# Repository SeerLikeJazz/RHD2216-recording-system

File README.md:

> 2022.05.21，上海，疫情在家，整理一下研究生期间的部分工作……

*Project was part of my work while at:*
* [EE-MEMS LAB](https://mems.sjtu.edu.cn/)
* Department of Micro/Nano Electronics
* Shanghai Jiao Tong University
* 2016.09-2019.03
### 探针型柔性MEMS脑机接口器件及采集电路研究
#### 系统介绍
* 研制了一种超薄的柔性探针型神经信号采集电极。
* 搭建了植入式神经信号采集电路的系统平台。
* 利用研制的柔性探针型神经信号采集电极和神经信号采集电路的系统平台做了体外测试验证实验。
#### 采集电路
电路主要包括Intan Technologies公司的16通道前端微弱生理信号采集芯片RHD2116，核心控制单元采用ST公司主频168M的STM32F407微控制器，数据传输采用内部集成全硬件TCP/IP协议栈+MAC+PHY以太网接口芯片W5500，通过UDP协议的方式实现硬件系统与上位机通信。

> 系统框图

电路尺寸4.2cm x 4.2cm，重量22g（包含电池），可以非常轻便地用于脑机接口应用和生物学实验。实验表明，16通道的采集系统输入噪声低至7 μV，每通道采样频率高达20 kHz，采样分辨率16位，满足植入式神经信号采集的要求。

> 硬件顶、底视图

#### 柔性电极
器件整体全部采用生物相容性材料，Au（厚度300nm）作为引线、电极点和焊盘，Parylene（厚度4μm）作为基底和绝缘层，PEG作为粘结材料贴附电极于PI管上，PI管（外径330μm）用作辅助植入的支撑材料。

通过电化学沉积导电聚合物PEDOT:PSS来提高了电极的电化学性能，并通过500次的循环伏安测试和10分钟的超声处理，验证了修饰后的电极的电化学稳定和聚合物结合力稳定性，测试并分析了电极的伏安特性和电化学阻抗谱。

研究了通过生物相容性的材料和PI管的组合，改进了柔性电极的准确植入位置的方法。

> 电极工艺图

> 电极实物图

> 电化学测试

> 电极贴附示意图

#### 实验测试
为了验证从电极前端到采集电路后端整个系统的准确性和功能稳定性，使用琼脂和PBS溶液模拟脑组织的环境，验证柔性微电极的准确植入性，辅助使用PI管和柔性电极在环境中的分离状况；使用微小信号发生器模拟了神经信号的幅值和频率，在体外模拟的脑组织环境中测试了信号采集、数据预处理、数据传输到上位机和上位机实时波形显示的在线实验。

> 测试实验示意图

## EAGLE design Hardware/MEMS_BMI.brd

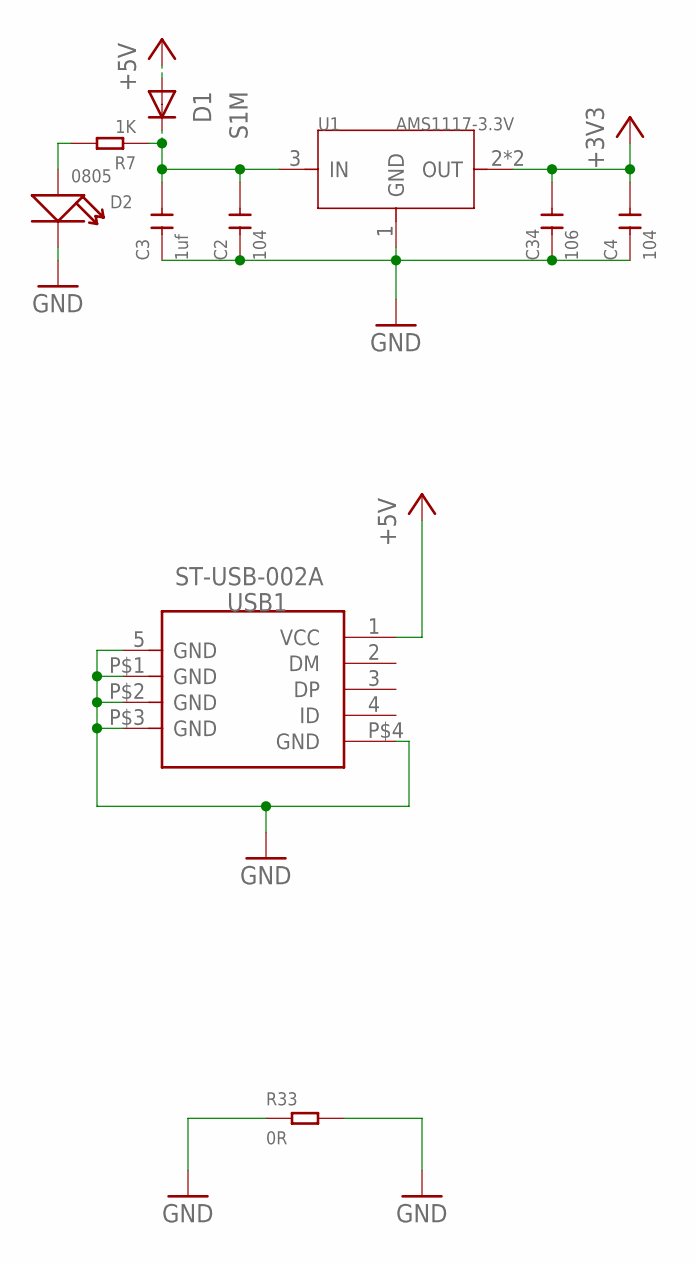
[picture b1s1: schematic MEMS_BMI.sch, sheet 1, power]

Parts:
C2, C4: 104; C0603
C3: 1uf; C0805
C34: 106; C0805
D1: S1M; SMA
D2: 0805; LED-0805
R7: 1K; R0603
R33: 0R; R0603
U1: AMS1117-3.3V; SOT-223
USB1: ST-USB-002A; MINIUSB5+4P-SMD-0.8-90D

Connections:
+3V3: C4.2, C34.2, U1.2 (OUT), U1.TER (OUT); also elsewhere on the board
+5V: D1.A, USB1.1 (VCC)
GND: C2.1, C3.1, C4.1, C34.1, D2.-, R33.1, R33.2, U1.1 (GND), USB1.5 (GND), USB1.P$1 (GND), USB1.P$2 (GND), USB1.P$3 (GND), USB1.P$4 (GND); also elsewhere on the board
unnamed: C2.2, C3.2, D1.C, R7.1, U1.3 (IN)
unnamed: D2.+, R7.2

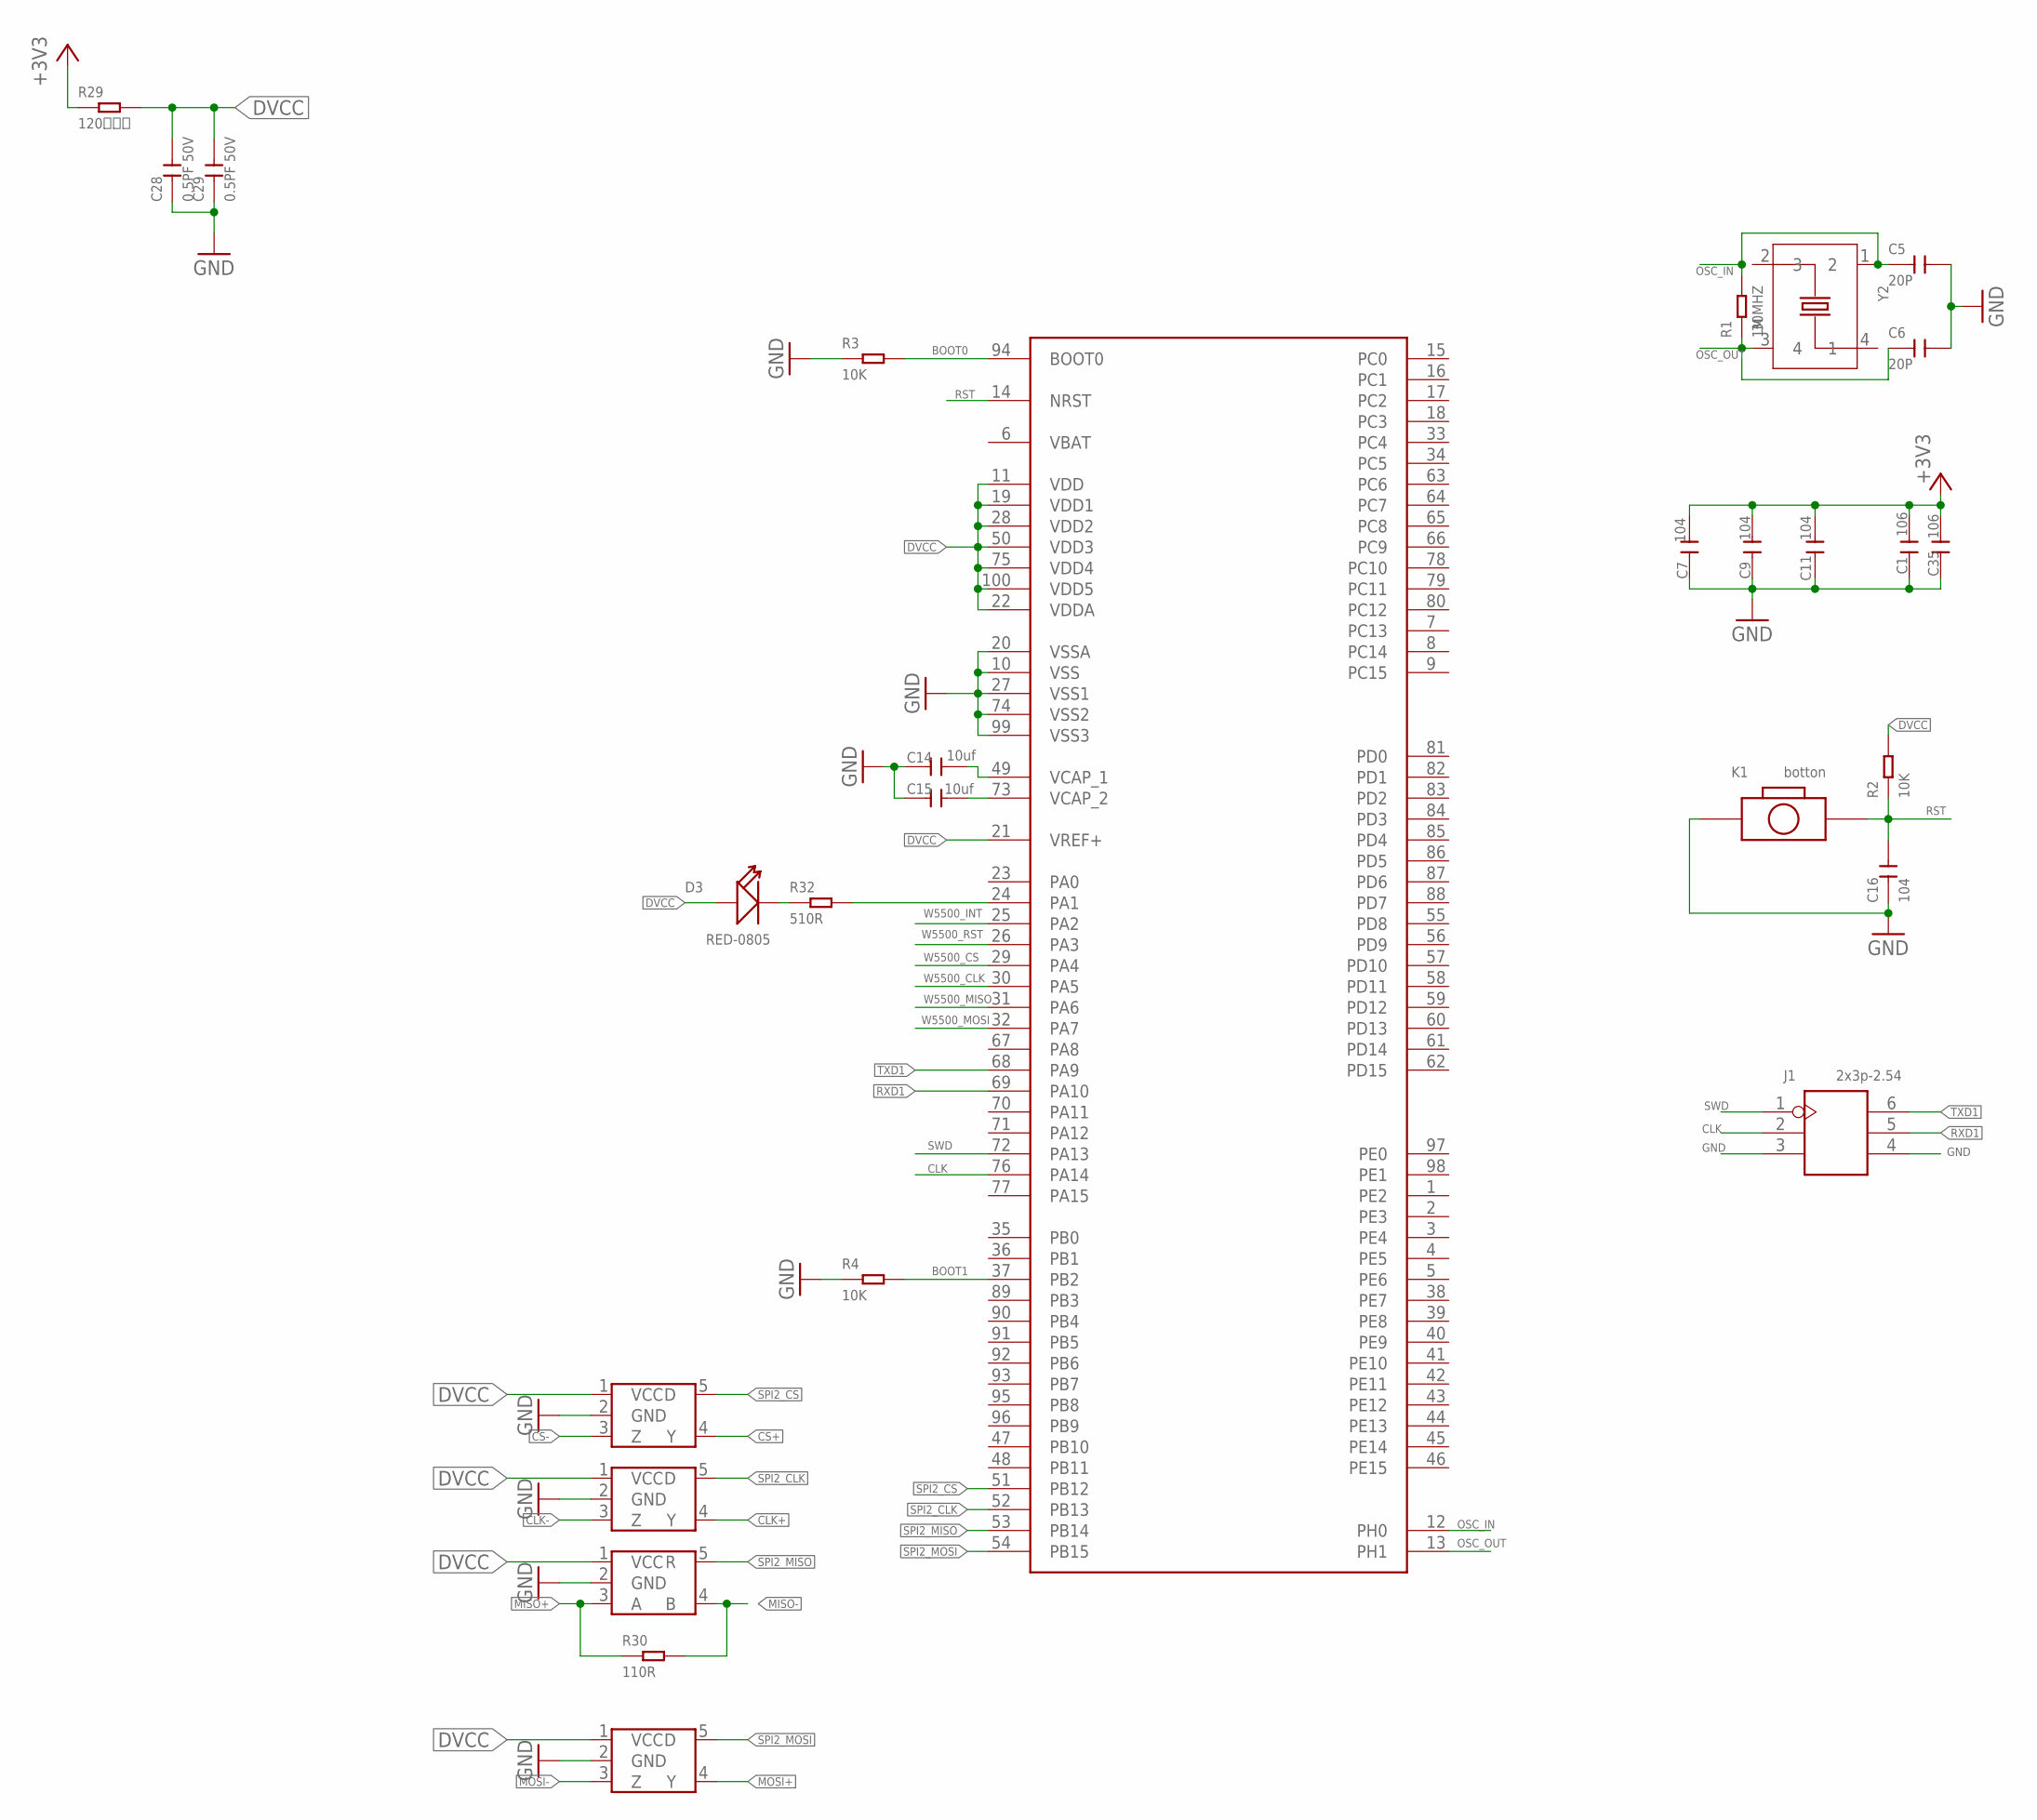
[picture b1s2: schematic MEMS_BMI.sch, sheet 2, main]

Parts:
C1, C35: 106; C0805
C5, C6: 20P; C0603
C7, C9, C11, C16: 104; C0603
C14, C15: 10uf; C0805
C28, C29: 0.5PF 50V; C0603
D3: RED-0805; LED-0805
J1: 2x3p-2.54; H2X3-2.54
K1: botton; SW2-SMD-3.0X6.0*2.5
LVDS1-1, LVDS1-2, LVDS1-3: SN65LVDS1; DBV_R-PDSO-G5
R1: 1M; R0603
R2, R3, R4: 10K; R0603
R29: 120欧磁珠; R0603
R30: 110R; R0603
R32: 510R; R0603
U$1: STM32F40XSTM32D40X; LQFP100
U$2: SN65LVDS2; DBV_R-PDSO-G5
Y2: 30MHZ; X4-SMD-3.2X2.5X0.7MM

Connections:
+3V3: C1.2, C7.1, C9.1, C11.1, C35.2, R29.1; also elsewhere on the board
BOOT0: R3.2, U$1.94 (BOOT0)
BOOT1: R4.2, U$1.37 (PB2)
CLK: J1.2, U$1.76 (PA14)
CLK+: LVDS1-2.4 (Y); also elsewhere on the board
CLK-: LVDS1-2.3 (Z); also elsewhere on the board
CS+: LVDS1-1.4 (Y); also elsewhere on the board
CS-: LVDS1-1.3 (Z); also elsewhere on the board
DVCC: C28.2, C29.2, D3.+, LVDS1-1.1 (VCC), LVDS1-2.1 (VCC), LVDS1-3.1 (VCC), R2.2, R29.2, U$1.11 (VDD), U$1.19 (VDD1), U$1.21 (VREF+), U$1.22 (VDDA), U$1.28 (VDD2), U$1.50 (VDD3), U$1.75 (VDD4), U$1.100 (VDD5), U$2.1 (VCC); also elsewhere on the board
GND: C1.1, C5.2, C6.2, C7.2, C9.2, C11.2, C14.1, C15.1, C16.1, C28.1, C29.1, C35.1, J1.3, J1.4, K1.1, LVDS1-1.2 (GND), LVDS1-2.2 (GND), LVDS1-3.2 (GND), R3.1, R4.1, U$1.10 (VSS), U$1.20 (VSSA), U$1.27 (VSS1), U$1.74 (VSS2), U$1.99 (VSS3), U$2.2 (GND); also elsewhere on the board
MISO+: R30.1, U$2.3 (A); also elsewhere on the board
MISO-: R30.2, U$2.4 (B); also elsewhere on the board
MOSI+: LVDS1-3.4 (Y); also elsewhere on the board
MOSI-: LVDS1-3.3 (Z); also elsewhere on the board
unnamed: C15.2, U$1.73 (VCAP_2)
unnamed: C14.2, U$1.49 (VCAP_1)
unnamed: D3.-, R32.1
unnamed: R32.2, U$1.24 (PA1)
OSC_IN: C5.1, R1.2, U$1.12 (PH0), Y2.1 (2)
OSC_OUT: C6.1, R1.1, U$1.13 (PH1), Y2.3 (4)
RST: C16.2, K1.2, R2.1, U$1.14 (NRST)
RXD1: J1.5, U$1.69 (PA10)
SPI2_CLK: LVDS1-2.5 (D), U$1.52 (PB13)
SPI2_CS: LVDS1-1.5 (D), U$1.51 (PB12)
SPI2_MISO: U$1.53 (PB14), U$2.5 (R)
SPI2_MOSI: LVDS1-3.5 (D), U$1.54 (PB15)
SWD: J1.1, U$1.72 (PA13)
TXD1: J1.6, U$1.68 (PA9)
W5500_CLK: U$1.30 (PA5); also elsewhere on the board
W5500_CS: U$1.29 (PA4); also elsewhere on the board
W5500_INT: U$1.25 (PA2); also elsewhere on the board
W5500_MISO: U$1.31 (PA6); also elsewhere on the board
W5500_MOSI: U$1.32 (PA7); also elsewhere on the board
W5500_RST: U$1.26 (PA3); also elsewhere on the board

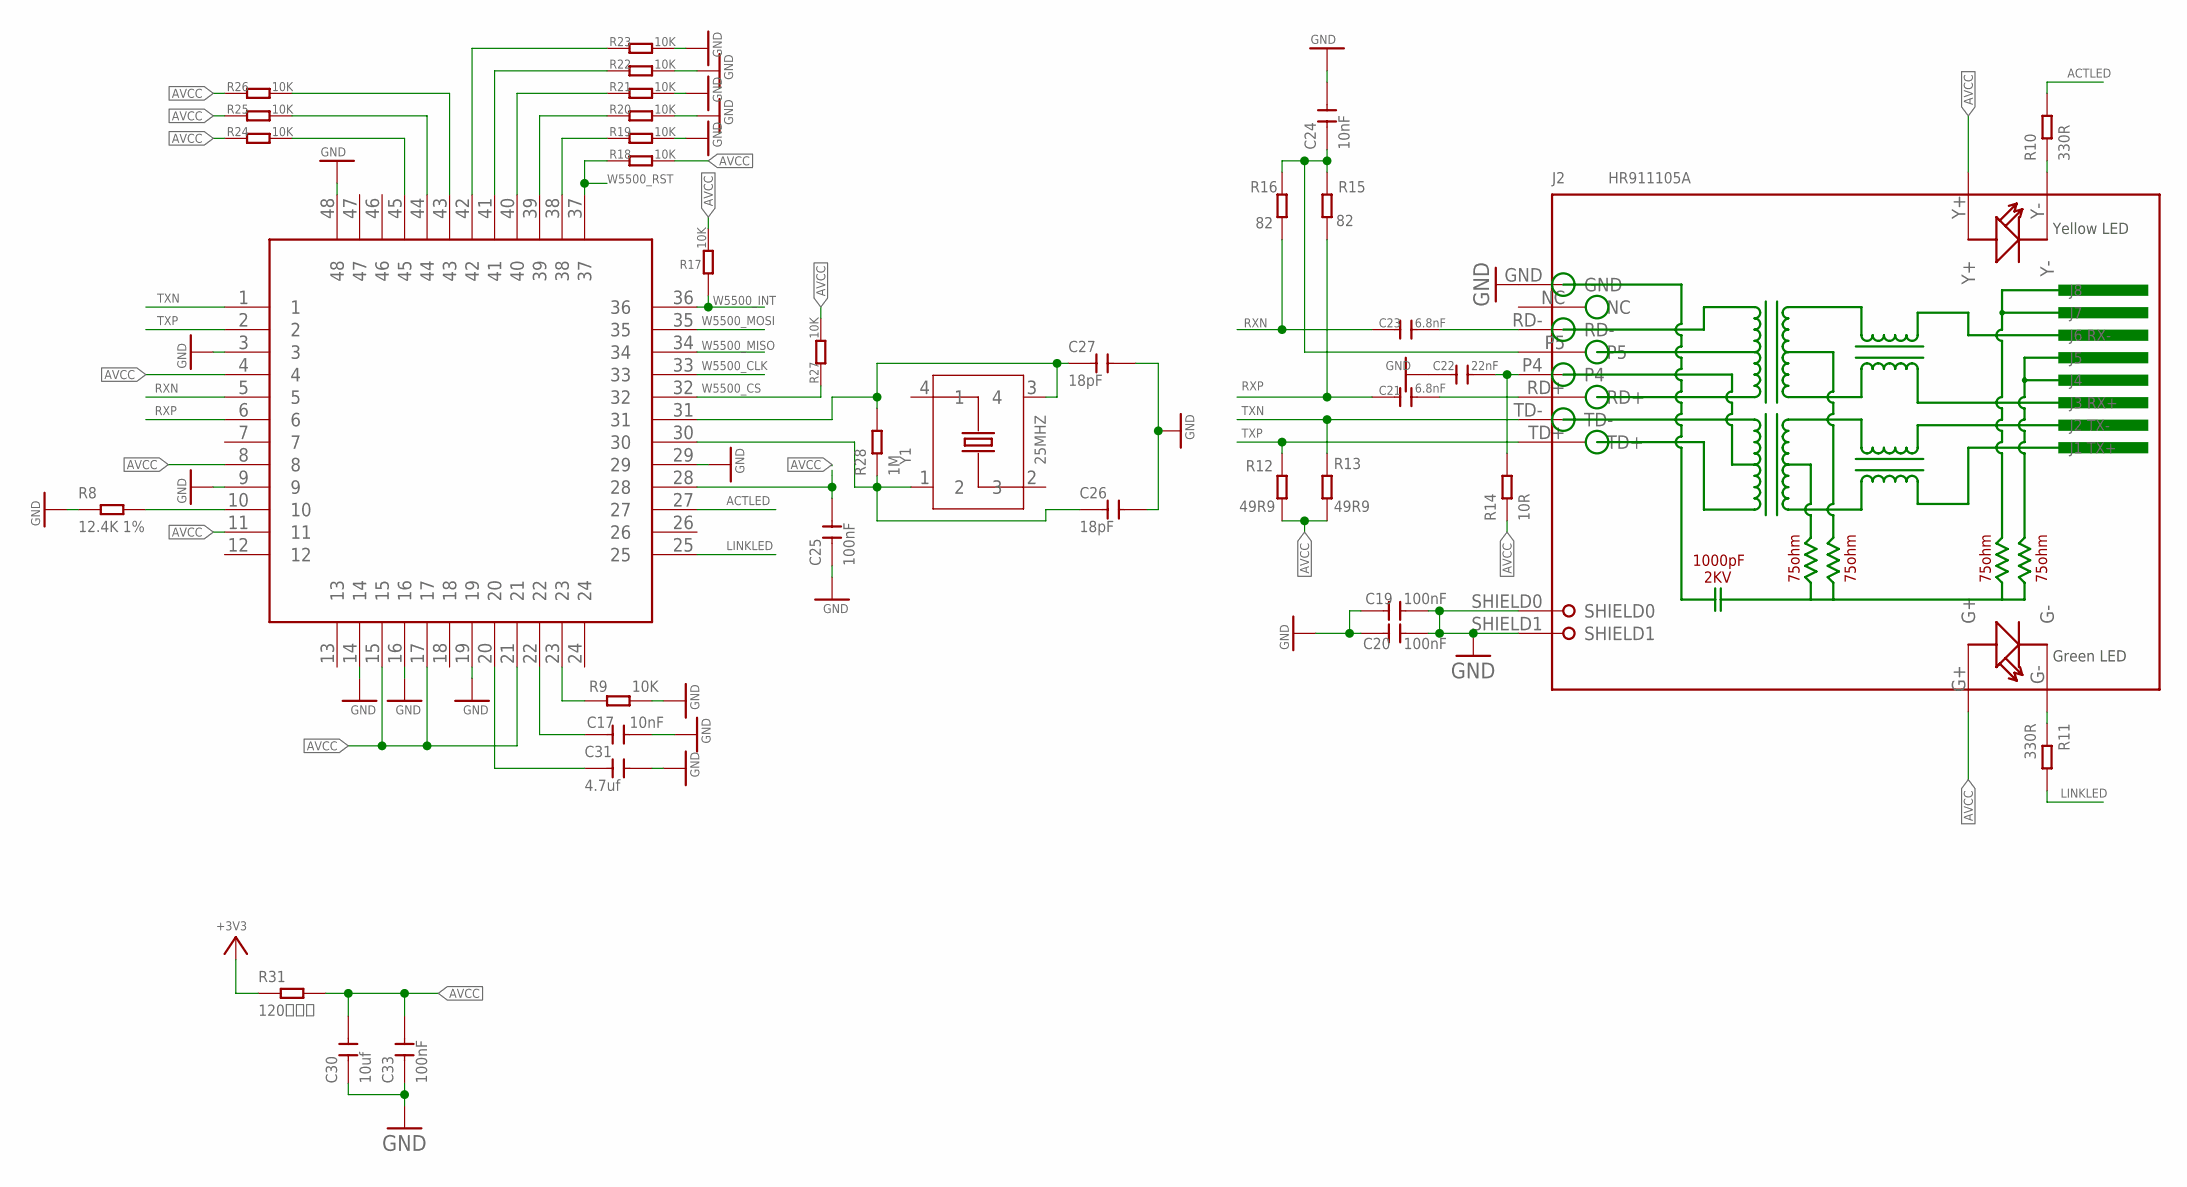
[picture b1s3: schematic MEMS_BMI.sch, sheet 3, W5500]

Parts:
C17, C24: 10nF; C0603
C19, C20, C25, C33: 100nF; C0603
C21, C23: 6.8nF; C0603
C22: 22nF; C0603
C26, C27: 18pF; C0603
C30: 10uf; C0805
C31: 4.7uf; C0805
J2: HR911105A; RJ45-12+2P-21.3X16.04X13.4MM
R8: 12.4K 1%; R0603
R9, R17, R18, R19, R20, R21, R22, R23, R24, R25, R26, R27: 10K; R0603
R10, R11: 330R; R0603
R12, R13: 49R9; R0603
R14: 10R; R0603
R15, R16: 82; R0603
R28: 1M; R0603
R31: 120欧磁珠; R0603
W5500-1: W5500; LQFP48
Y1: 25MHZ; X4-SMD-3.2X2.5X0.7MM

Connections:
+3V3: R31.1; also elsewhere on the board
ACTLED: R10.2, W5500-1.27
AVCC: C25.2, C30.2, C33.2, J2.G+, J2.Y+, R12.1, R13.1, R14.1, R17.2, R18.2, R24.1, R25.1, R26.1, R27.2, R31.2, W5500-1.4, W5500-1.8, W5500-1.11, W5500-1.15, W5500-1.17, W5500-1.21, W5500-1.28
GND: C17.2, C19.1, C19.2, C20.1, C20.2, C22.1, C24.2, C25.1, C26.2, C27.2, C30.1, C31.2, C33.1, J2.GND, J2.SHIELD0, J2.SHIELD1, R8.1, R9.2, R19.2, R20.2, R21.2, R22.2, R23.2, W5500-1.3, W5500-1.9, W5500-1.14, W5500-1.16, W5500-1.19, W5500-1.29, W5500-1.48; also elsewhere on the board
LINKLED: R11.2, W5500-1.25
unnamed: R9.1, W5500-1.23
unnamed: C17.1, W5500-1.22
unnamed: C31.1, W5500-1.20
unnamed: J2.G-, R11.1
unnamed: J2.Y-, R10.1
unnamed: R24.2, W5500-1.45
unnamed: R8.2, W5500-1.10
unnamed: R25.2, W5500-1.44
unnamed: C21.2, J2.RD+
unnamed: C22.2, J2.P4, R14.2
unnamed: R26.2, W5500-1.43
unnamed: C23.2, J2.RD-
unnamed: C27.1, R28.2, W5500-1.31, Y1.3 (4)
unnamed: R19.1, W5500-1.38
unnamed: C24.1, J2.P5, R15.2, R16.2
unnamed: R20.1, W5500-1.39
unnamed: R21.1, W5500-1.40
unnamed: R22.1, W5500-1.41
unnamed: R23.1, W5500-1.42
unnamed: C26.1, R28.1, W5500-1.30, Y1.1 (2)
RXN: C23.1, R16.1, W5500-1.5
RXP: C21.1, R15.1, W5500-1.6
TXN: J2.TD-, R13.2, W5500-1.1
TXP: J2.TD+, R12.2, W5500-1.2
W5500_CLK: W5500-1.33; also elsewhere on the board
W5500_CS: R27.1, W5500-1.32; also elsewhere on the board
W5500_INT: R17.1, W5500-1.36; also elsewhere on the board
W5500_MISO: W5500-1.34; also elsewhere on the board
W5500_MOSI: W5500-1.35; also elsewhere on the board
W5500_RST: R18.1, W5500-1.37; also elsewhere on the board

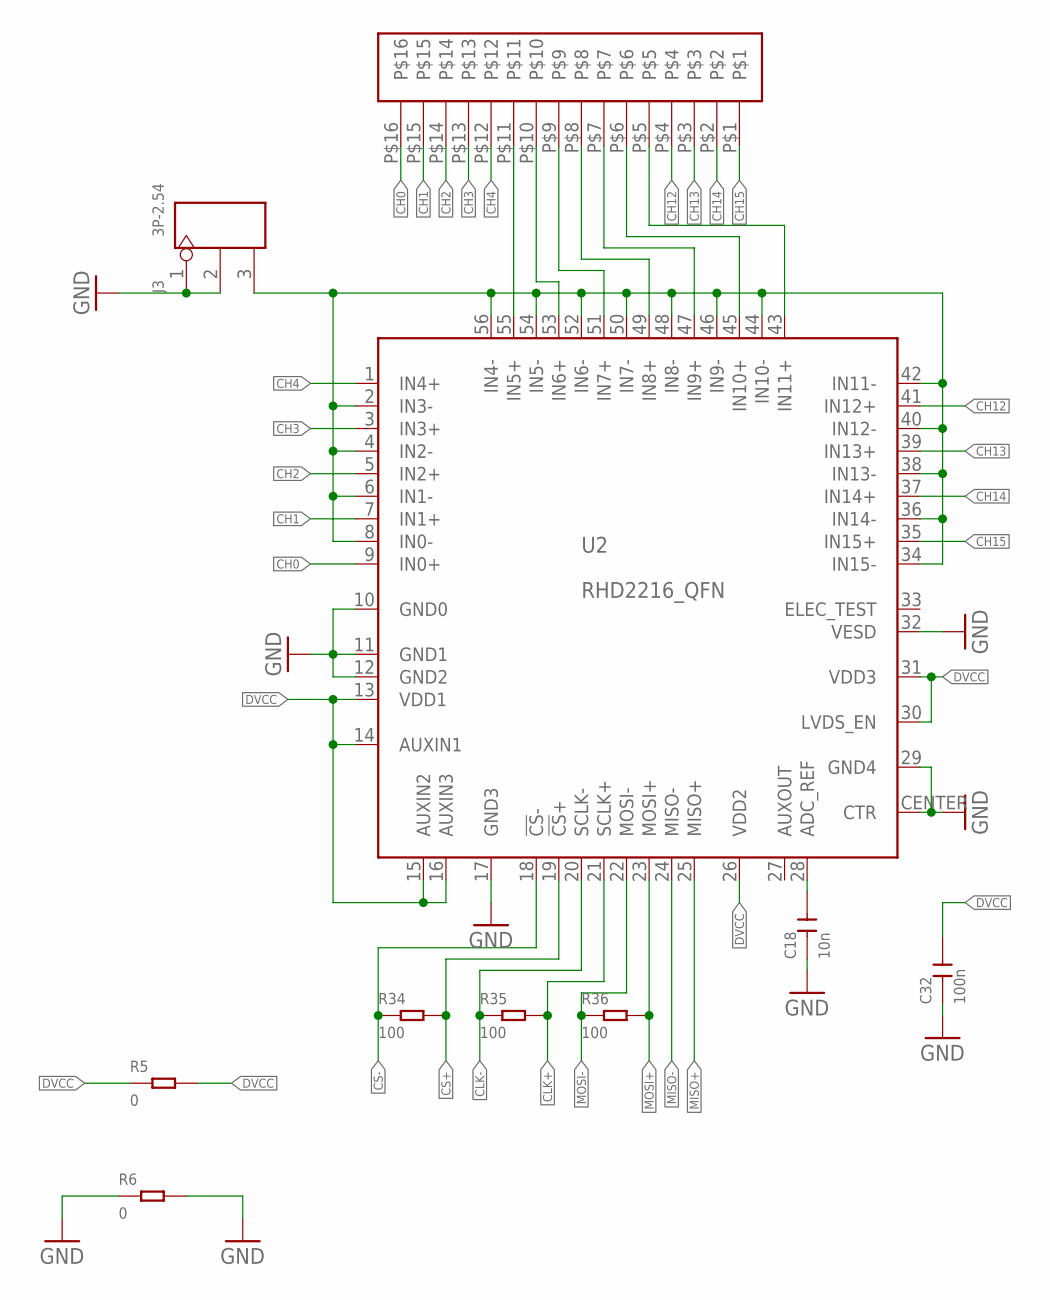
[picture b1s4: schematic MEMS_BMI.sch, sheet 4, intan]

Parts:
C18: 10n; C0603
C32: 100n; C0603
J3: 3P-2.54; H3-2.54
R5, R6: 0; R0603
R34, R35, R36: 100; R0603
U2: RHD2216_QFN; QFN56_8_X_8_LARGE
U$3: PROBE; PROBE-16-PIN

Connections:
CH0: U2.9 (IN0+), U$3.P$16
CH1: U2.7 (IN1+), U$3.P$15
CH2: U2.5 (IN2+), U$3.P$14
CH3: U2.3 (IN3+), U$3.P$13
CH4: U2.1 (IN4+), U$3.P$12
CH12: U2.41 (IN12+), U$3.P$4
CH13: U2.39 (IN13+), U$3.P$3
CH14: U2.37 (IN14+), U$3.P$2
CH15: U2.35 (IN15+), U$3.P$1
CLK+: R35.2, U2.21 (SCLK+); also elsewhere on the board
CLK-: R35.1, U2.20 (SCLK-); also elsewhere on the board
CS+: R34.2, U2.19 (!CS!+); also elsewhere on the board
CS-: R34.1, U2.18 (!CS!-); also elsewhere on the board
DVCC: C32.2, R5.1, R5.2, U2.13 (VDD1), U2.14 (AUXIN1), U2.15 (AUXIN2), U2.16 (AUXIN3), U2.26 (VDD2), U2.30 (LVDS_EN), U2.31 (VDD3); also elsewhere on the board
GND: C18.1, C32.1, J3.1, J3.2, R6.1, R6.2, U2.10 (GND0), U2.11 (GND1), U2.12 (GND2), U2.17 (GND3), U2.29 (GND4), U2.32 (VESD), U2.CENTER (CTR); also elsewhere on the board
MISO+: U2.25 (MISO+); also elsewhere on the board
MISO-: U2.24 (MISO-); also elsewhere on the board
MOSI+: R36.2, U2.23 (MOSI+); also elsewhere on the board
MOSI-: R36.1, U2.22 (MOSI-); also elsewhere on the board
unnamed: C18.2, U2.28 (ADC_REF)
unnamed: J3.3, U2.2 (IN3-), U2.4 (IN2-), U2.6 (IN1-), U2.8 (IN0-), U2.34 (IN15-), U2.36 (IN14-), U2.38 (IN13-), U2.40 (IN12-), U2.42 (IN11-), U2.44 (IN10-), U2.46 (IN9-), U2.48 (IN8-), U2.50 (IN7-), U2.52 (IN6-), U2.54 (IN5-), U2.56 (IN4-)
unnamed: U2.55 (IN5+), U$3.P$11
unnamed: U2.53 (IN6+), U$3.P$10
unnamed: U2.51 (IN7+), U$3.P$9
unnamed: U2.49 (IN8+), U$3.P$8
unnamed: U2.47 (IN9+), U$3.P$7
unnamed: U2.45 (IN10+), U$3.P$6
unnamed: U2.43 (IN11+), U$3.P$5

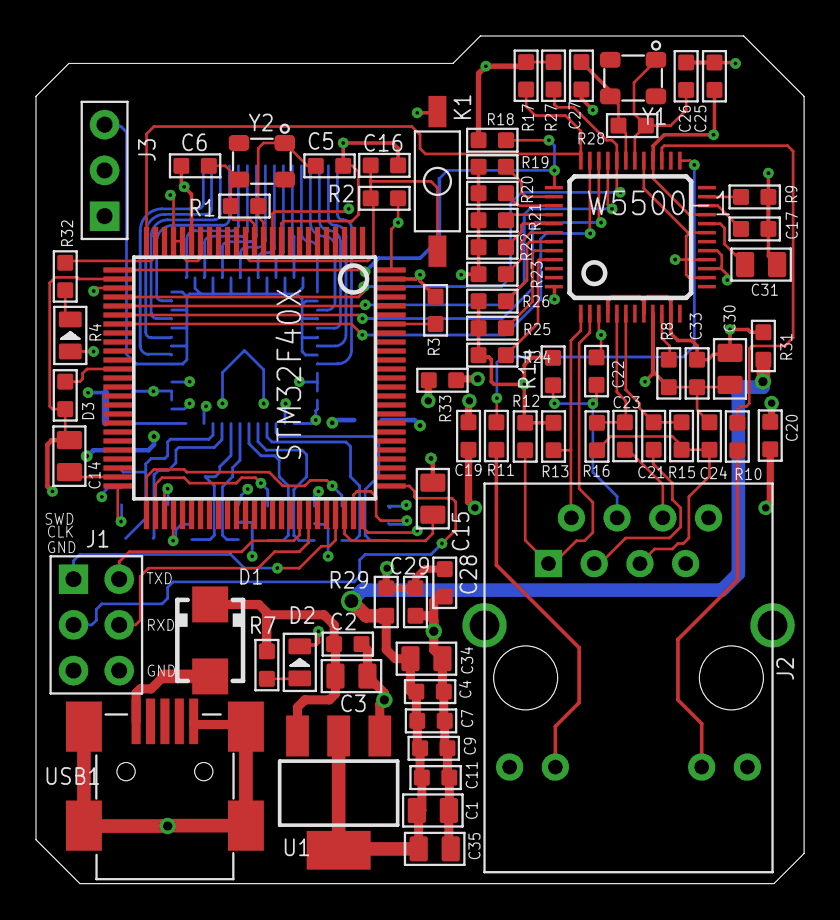
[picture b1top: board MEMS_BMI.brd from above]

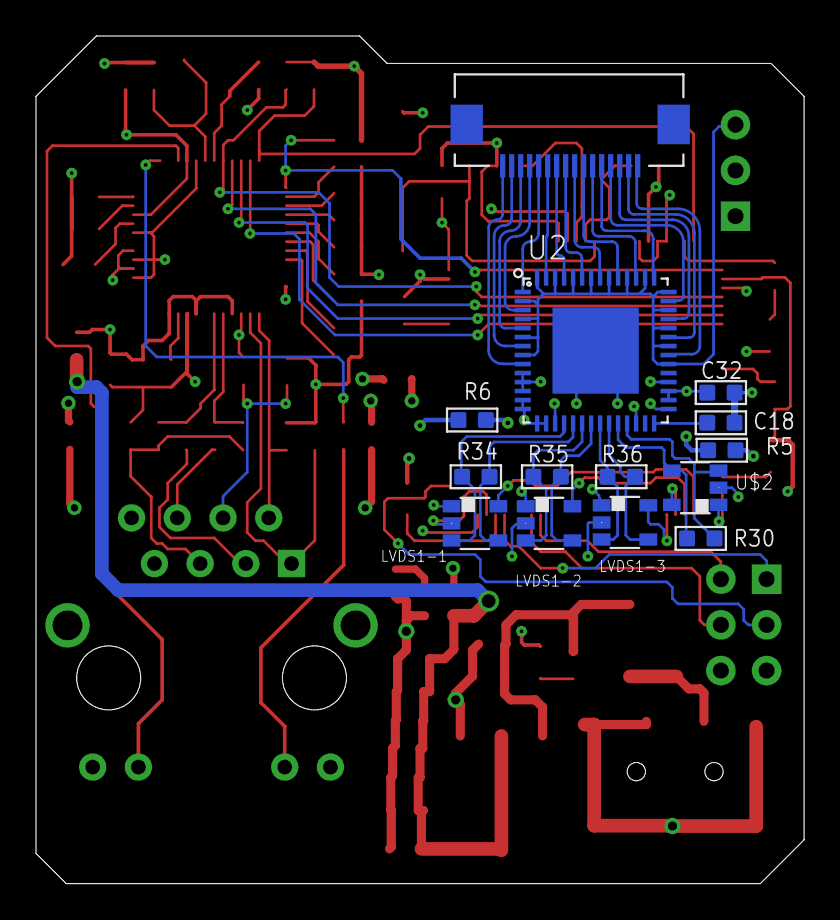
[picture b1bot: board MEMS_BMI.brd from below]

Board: 4 copper layers, 42.7 x 47.1 mm, 86 parts (14 on the bottom side), 82 nets.

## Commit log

2022-05-21 Add project
2022-05-21 Add GUI-python(Write by Yan xiaotian)
